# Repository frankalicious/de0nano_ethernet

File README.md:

| Artikel | Shop | Bestellnummer | Anzahl |
|---------|------|---------------|--------|
| Buchsenl. 2x10 pol wkl. | csd-electronics | 014-B210W | 2|
| Buchsenl. 2x20 pol gerade | csd-electronics | 014-B220G | 1|

ordered from osh park on 2014-12-12
https://oshpark.com/shared_projects/RDXAlT9o

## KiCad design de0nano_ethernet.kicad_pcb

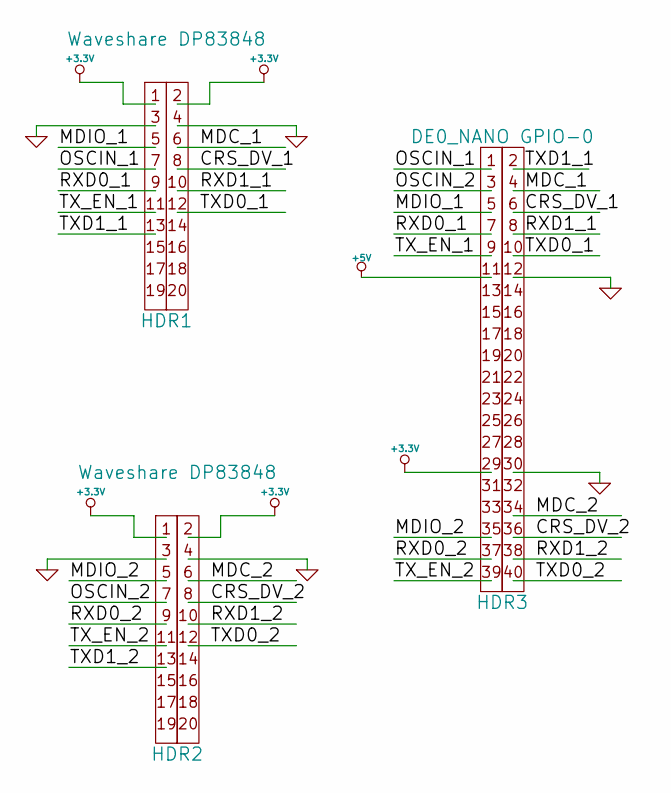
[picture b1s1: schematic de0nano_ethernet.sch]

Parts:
HDR1, HDR2: Waveshare DP83848; AB2_HDR_M10-2V
HDR3: DE0_NANO GPIO-0; AB2_HDR_M20-2V

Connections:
+3.3V: HDR1.1, HDR1.2, HDR2.1, HDR2.2, HDR3.29
+5V: HDR3.11
/CRS_DV_1: HDR1.8, HDR3.6
/CRS_DV_2: HDR2.8, HDR3.36
/MDC_1: HDR1.6, HDR3.4
/MDC_2: HDR2.6, HDR3.34
/MDIO_1: HDR1.5, HDR3.5
/MDIO_2: HDR2.5, HDR3.35
/OSCIN_1: HDR1.7, HDR3.1
/OSCIN_2: HDR2.7, HDR3.3
/RXD0_1: HDR1.9, HDR3.7
/RXD0_2: HDR2.9, HDR3.37
/RXD1_1: HDR1.10, HDR3.8
/RXD1_2: HDR2.10, HDR3.38
/TXD0_1: HDR1.12, HDR3.10
/TXD0_2: HDR2.12, HDR3.40
/TXD1_1: HDR1.13, HDR3.2
/TXD1_2: HDR2.13
/TX_EN_1: HDR1.11, HDR3.9
/TX_EN_2: HDR2.11, HDR3.39
GND: HDR1.3, HDR1.4, HDR2.3, HDR2.4, HDR3.12, HDR3.30

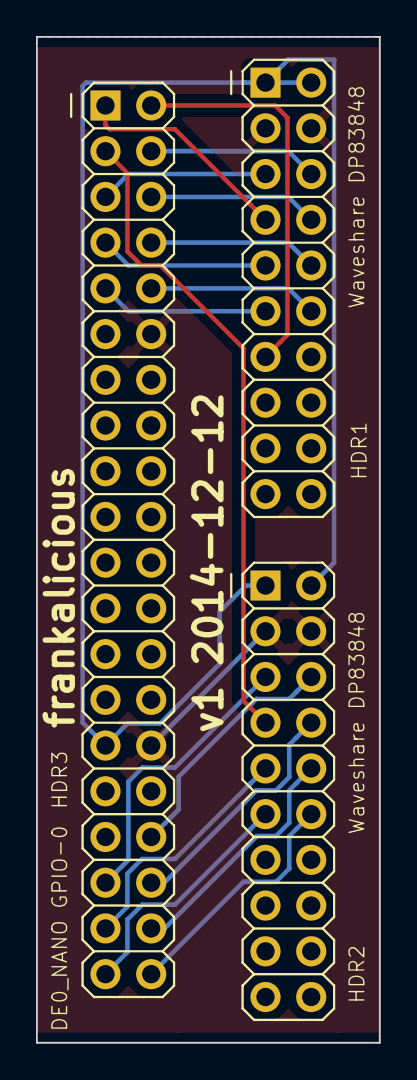
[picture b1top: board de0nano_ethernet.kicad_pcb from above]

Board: 2 copper layers, 19.0 x 55.9 mm, 3 parts (0 on the bottom side), 19 nets.

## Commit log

2014-12-11 add README
2014-12-11 add version and designer to silkscreen
    create gerber files and zip file for osk park
2015-04-05 Update README.md
    add link to shared osh project
